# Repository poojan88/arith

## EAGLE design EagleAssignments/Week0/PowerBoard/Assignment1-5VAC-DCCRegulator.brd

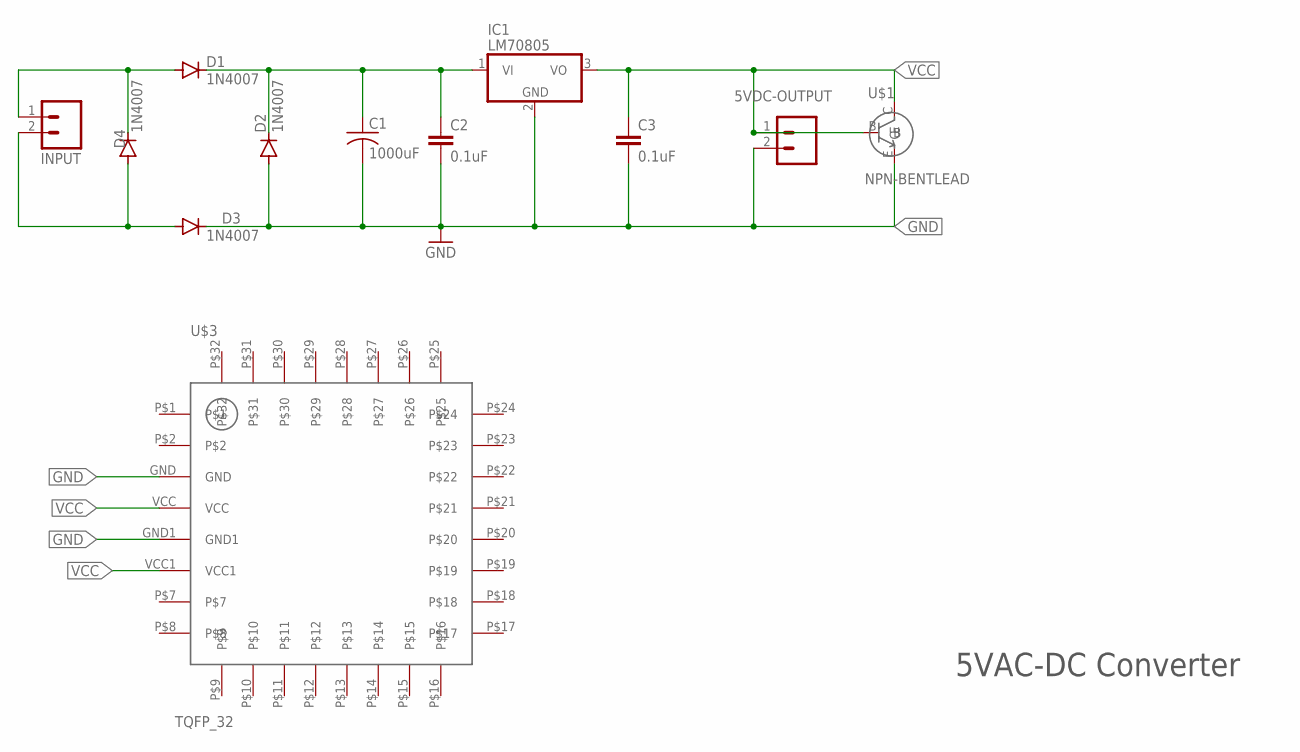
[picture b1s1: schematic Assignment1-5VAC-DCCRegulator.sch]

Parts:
5VDC-OUTPUT: M02; 02P
C1: 1000uF; C025-024X044
C2, C3: 0.1uF; C025-025X050
D1, D2, D3, D4: 1N4007; DO41-10
IC1: LM70805; TO220V
INPUT: M02; 02P
U$1: NPN-BENTLEAD; BENT-LEAD
U$3: TQFP_32

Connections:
GND: 5VDC-OUTPUT.2, C1.2, C2.2, C3.2, D2.A, D3.C, IC1.2 (GND), U$1.E, U$3.GND, U$3.GND1
unnamed: D1.A, D4.C, INPUT.1
unnamed: D3.A, D4.A, INPUT.2
unnamed: C1.1, C2.1, D1.C, D2.C, IC1.1 (VI)
VCC: 5VDC-OUTPUT.1, C3.1, IC1.3 (VO), U$1.B, U$1.C, U$3.VCC, U$3.VCC1

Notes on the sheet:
5VAC-DC Converter

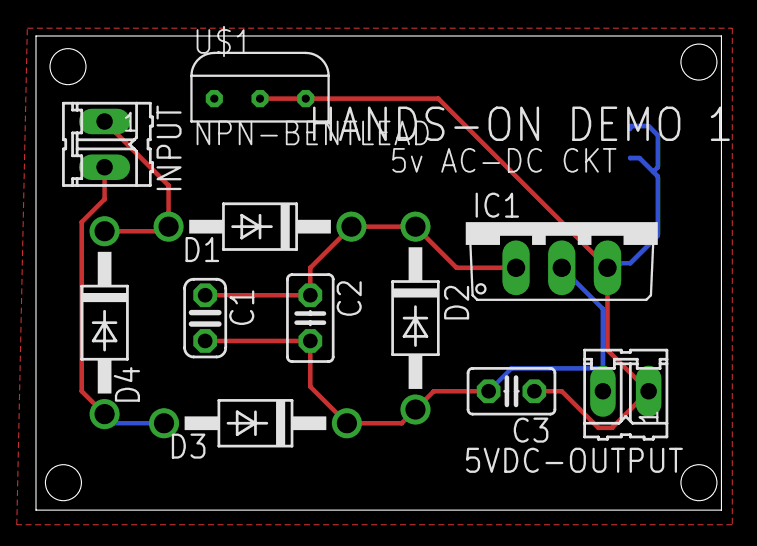
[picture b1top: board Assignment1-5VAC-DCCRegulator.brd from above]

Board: 2 copper layers, 38.1 x 26.3 mm, 12 parts (1 on the bottom side), 5 nets.

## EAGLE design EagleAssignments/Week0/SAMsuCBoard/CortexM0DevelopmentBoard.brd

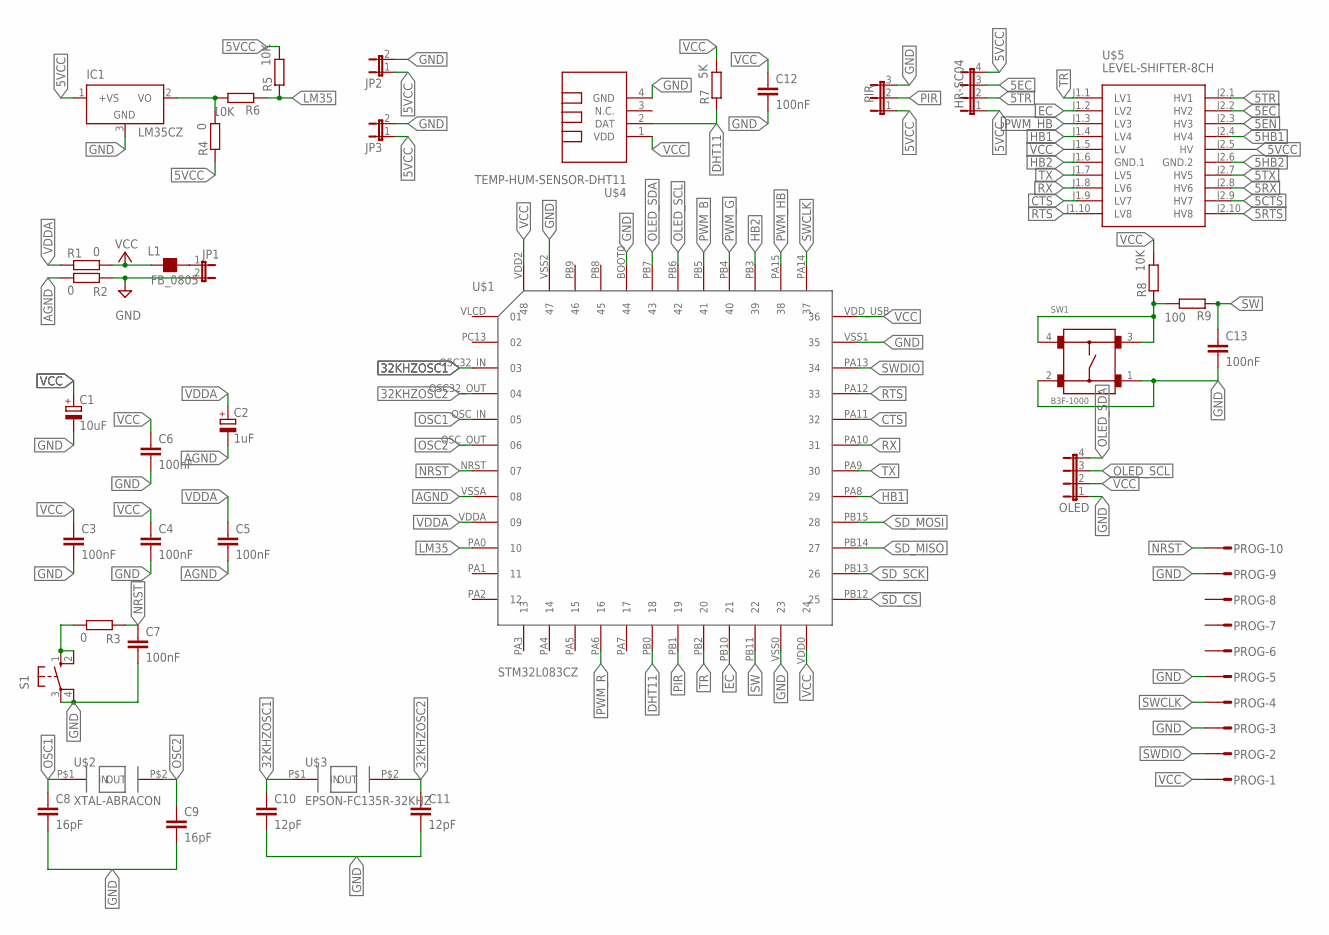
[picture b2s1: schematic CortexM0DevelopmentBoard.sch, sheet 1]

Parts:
C1: 10uF; 139CLL-2R
C2: 1uF; 139CLL-2R
C3, C4, C5, C6, C7, C12, C13: 100nF; C0805
C8, C9: 16pF; C0805
C10, C11: 12pF; C0805
HR-SC04: JP4E; JP4
IC1: LM35CZ; TO92
JP1, JP2, JP3: JP1E; JP1
L1: FB_0805; L0805
OLED: JP4E; JP4
PIR: JP2E; JP2
PROG: S10P
R1, R2, R3, R4: 0; R0805
R5, R6, R8: 10K; R0805
R7: 5K; R0805
R9: 100; R0805
S1: 10-XX; B3F-10XX
SW1: B3F-1000
U$1: STM32L083CZ; STM32L083CZ-LQFP48
U$2: XTAL-ABRACON; XTAL-ABRACON-SMD
U$3: EPSON-FC135R-32KHZ; EPSON-32KHZ-FC135R
U$4: TEMP-HUM-SENSOR-DHT11
U$5: LEVEL-SHIFTER-8CH

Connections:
5CTS: U$5.J2.9 (HV7); also elsewhere on the board
5EC: HR-SC04.3, U$5.J2.2 (HV2)
5EN: U$5.J2.3 (HV3); also elsewhere on the board
5HB1: U$5.J2.4 (HV4); also elsewhere on the board
5HB2: U$5.J2.6 (GND.2); also elsewhere on the board
5RTS: U$5.J2.10 (HV8); also elsewhere on the board
5RX: U$5.J2.8 (HV6); also elsewhere on the board
5TR: HR-SC04.2, U$5.J2.1 (HV1)
5TX: U$5.J2.7 (HV5); also elsewhere on the board
5VCC: HR-SC04.1, HR-SC04.4, IC1.1 (+VS), JP2.1, PIR.1, R5.2, U$5.J2.5 (HV); also elsewhere on the board
32KHZOSC1: C10.1, U$1.OSC32_IN (03), U$3.P$1 (IN)
32KHZOSC2: C11.1, U$1.OSC32_OUT (04), U$3.P$2 (OUT)
!5VCC: JP3.1, R4.1
!SD_CS: U$1.PB12 (25); also elsewhere on the board
AGND: C2.-, C5.2, R2.1, U$1.VSSA (08)
CTS: U$1.PA11 (32), U$5.J1.9 (LV7)
DHT11: R7.1, U$1.PB0 (18), U$4.2 (DAT)
EC: U$1.PB10 (21), U$5.J1.2 (LV2)
GND: C1.-, C3.2, C4.2, C6.2, C7.2, C8.2, C9.2, C10.2, C11.2, C12.2, C13.2, IC1.3 (GND), JP1.2, JP2.2, JP3.2, OLED.1, PIR.3, PROG.3, PROG.5, PROG.9, R2.2, S1.3, S1.4 (P1), SW1.1, SW1.2, U$1.BOOT0 (44), U$1.VSS0 (23), U$1.VSS1 (35), U$1.VSS2 (47), U$4.4 (GND); also elsewhere on the board
HB1: U$1.PA8 (29), U$5.J1.4 (LV4)
HB2: U$1.PB3 (39), U$5.J1.6 (GND.1)
LM35: R5.1, R6.1, U$1.PA0 (10)
unnamed: JP1.1, L1.2
unnamed: R3.1, S1.1 (S), S1.2 (S1)
unnamed: IC1.2 (VO), R4.2, R6.2
unnamed: R8.1, R9.2, SW1.3, SW1.4
NRST: C7.1, PROG.10, R3.2, U$1.NRST (07)
OLED_SCL: OLED.3, U$1.PB6 (42)
OLED_SDA: OLED.4, U$1.PB7 (43)
OSC1: C8.1, U$1.OSC_IN (05), U$2.P$1 (IN)
OSC2: C9.1, U$1.OSC_OUT (06), U$2.P$2 (OUT)
PIR: PIR.2, U$1.PB1 (19)
PWM_B: U$1.PB5 (41); also elsewhere on the board
PWM_G: U$1.PB4 (40); also elsewhere on the board
PWM_HB: U$1.PA15 (38), U$5.J1.3 (LV3)
PWM_R: U$1.PA6 (16); also elsewhere on the board
RTS: U$1.PA12 (33), U$5.J1.10 (LV8)
RX: U$1.PA10 (31), U$5.J1.8 (LV6)
SD_MISO: U$1.PB14 (27); also elsewhere on the board
SD_MOSI: U$1.PB15 (28); also elsewhere on the board
SD_SCK: U$1.PB13 (26); also elsewhere on the board
SW: C13.1, R9.1, U$1.PB11 (22)
SWCLK: PROG.4, U$1.PA14 (37)
SWDIO: PROG.2, U$1.PA13 (34)
TR: U$1.PB2 (20), U$5.J1.1 (LV1)
TX: U$1.PA9 (30), U$5.J1.7 (LV5)
VCC: C1.+, C3.1, C4.1, C6.1, C12.1, L1.1, OLED.2, PROG.1, R1.2, R7.2, R8.2, U$1.VDD0 (24), U$1.VDD2 (48), U$1.VDD_USB (36), U$4.1 (VDD), U$5.J1.5 (LV); also elsewhere on the board
VDDA: C2.+, C5.1, R1.1, U$1.VDDA (09)

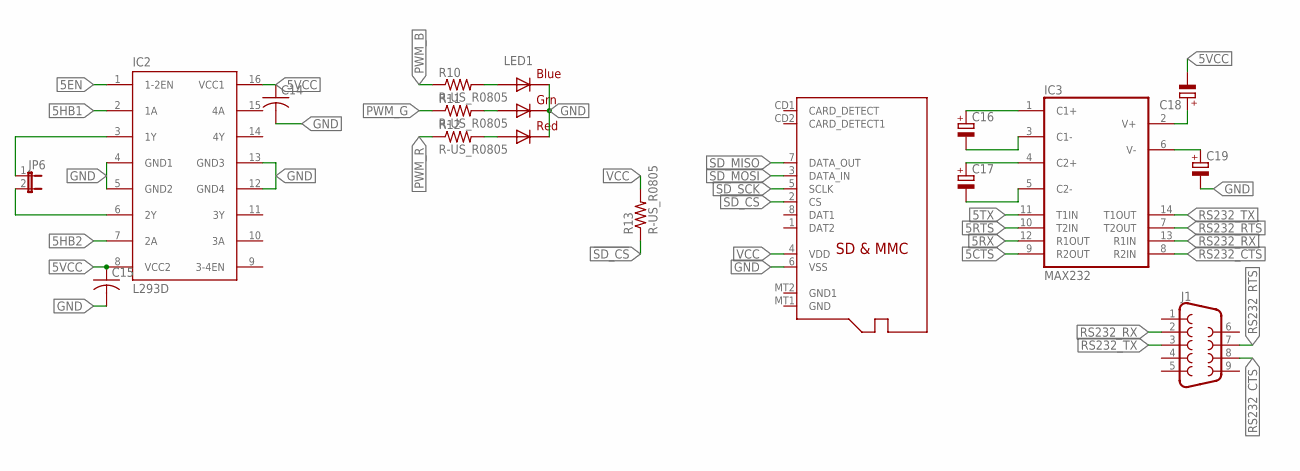
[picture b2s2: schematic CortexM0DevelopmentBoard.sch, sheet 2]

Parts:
C14, C15: C-US_CHIP-0805(2012-METRIC); CAPC2012X110
C16, C17, C18, C19: C-POL_TANTALUM-1206(3216-METRIC); CAPMP3216X180N
IC2: L293D; DIL16
IC3: MAX232; DIL16
J1: DB9FEMALE; DB9
JP6: JP1E; JP1
LED1: RGBLED5050
R10, R11, R12, R13: R-US_R0805; R0805
U$6: MICROSD

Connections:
5CTS: IC3.9 (R2OUT); also elsewhere on the board
5EN: IC2.1 (1-2EN); also elsewhere on the board
5HB1: IC2.2 (1A); also elsewhere on the board
5HB2: IC2.7 (2A); also elsewhere on the board
5RTS: IC3.10 (T2IN); also elsewhere on the board
5RX: IC3.12 (R1OUT); also elsewhere on the board
5TX: IC3.11 (T1IN); also elsewhere on the board
5VCC: C14.1, C15.1, C18.2 (-), IC2.8 (VCC2), IC2.16 (VCC1); also elsewhere on the board
!SD_CS: R13.1, U$6.2 (CS); also elsewhere on the board
GND: C14.2, C15.2, C19.2 (-), IC2.4 (GND1), IC2.5 (GND2), IC2.12 (GND4), IC2.13 (GND3), IC3.15 (GND), LED1.4 (BLUE_C), LED1.5 (RED_C), LED1.6 (GREEN_C), U$6.6 (VSS); also elsewhere on the board
unnamed: LED1.3 (BLUE_A), R10.2
unnamed: LED1.1 (GREEN_A), R11.2
unnamed: LED1.2 (RED_A), R12.2
unnamed: C16.1 (+), IC3.1 (C1+)
unnamed: C16.2 (-), IC3.3 (C1-)
unnamed: C17.1 (+), IC3.4 (C2+)
unnamed: C17.2 (-), IC3.5 (C2-)
unnamed: IC2.3 (1Y), JP6.1
unnamed: IC2.6 (2Y), JP6.2
unnamed: C18.1 (+), IC3.2 (V+)
unnamed: C19.1 (+), IC3.6 (V-)
PWM_B: R10.1; also elsewhere on the board
PWM_G: R11.1; also elsewhere on the board
PWM_R: R12.1; also elsewhere on the board
RS232_CTS: IC3.8 (R2IN), J1.8
RS232_RTS: IC3.7 (T2OUT), J1.7
RS232_RX: IC3.13 (R1IN), J1.2
RS232_TX: IC3.14 (T1OUT), J1.3
SD_MISO: U$6.7 (DATA_OUT); also elsewhere on the board
SD_MOSI: U$6.3 (DATA_IN); also elsewhere on the board
SD_SCK: U$6.5 (SCLK); also elsewhere on the board
VCC: IC3.16 (VCC), R13.2, U$6.4 (VDD); also elsewhere on the board

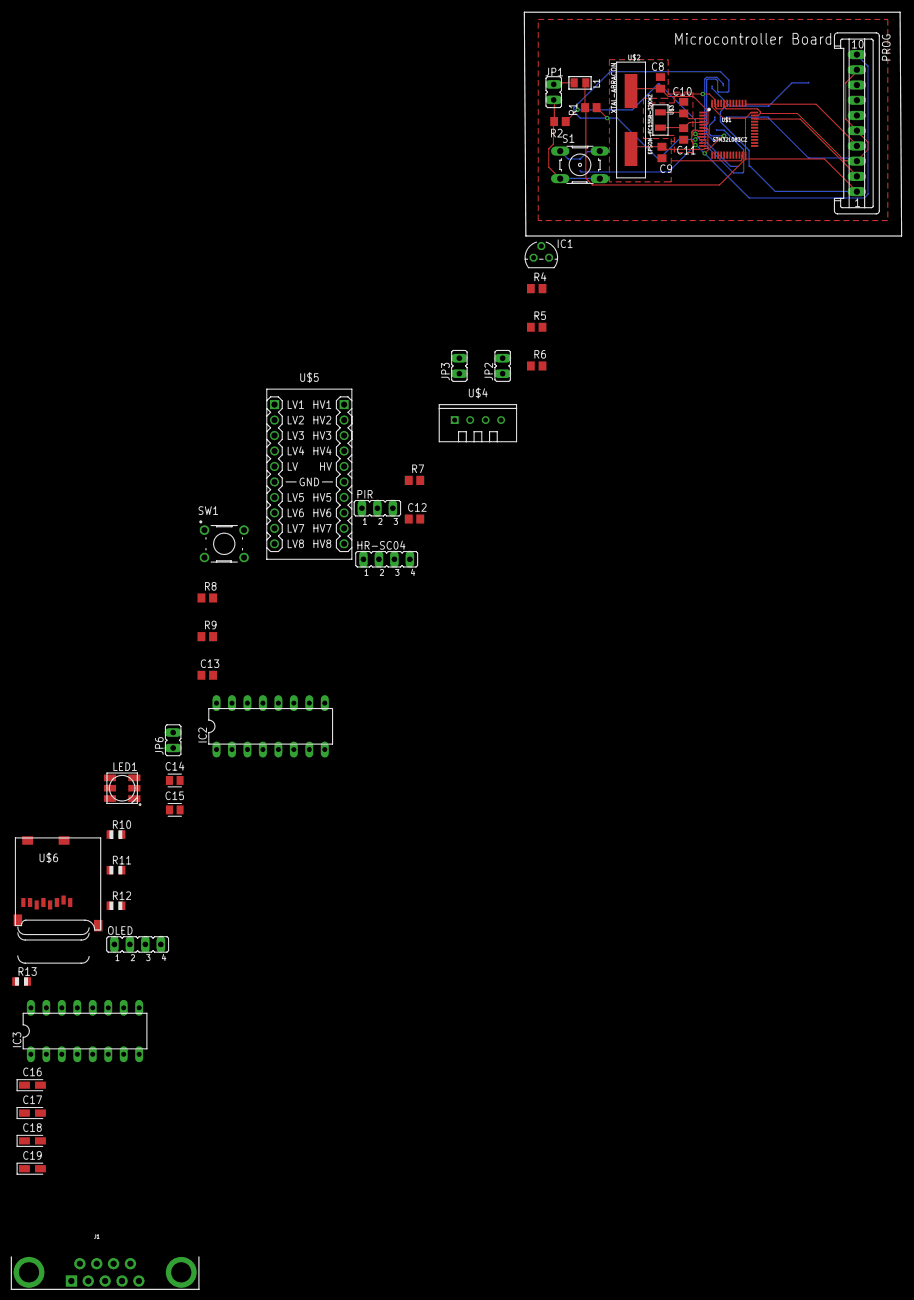
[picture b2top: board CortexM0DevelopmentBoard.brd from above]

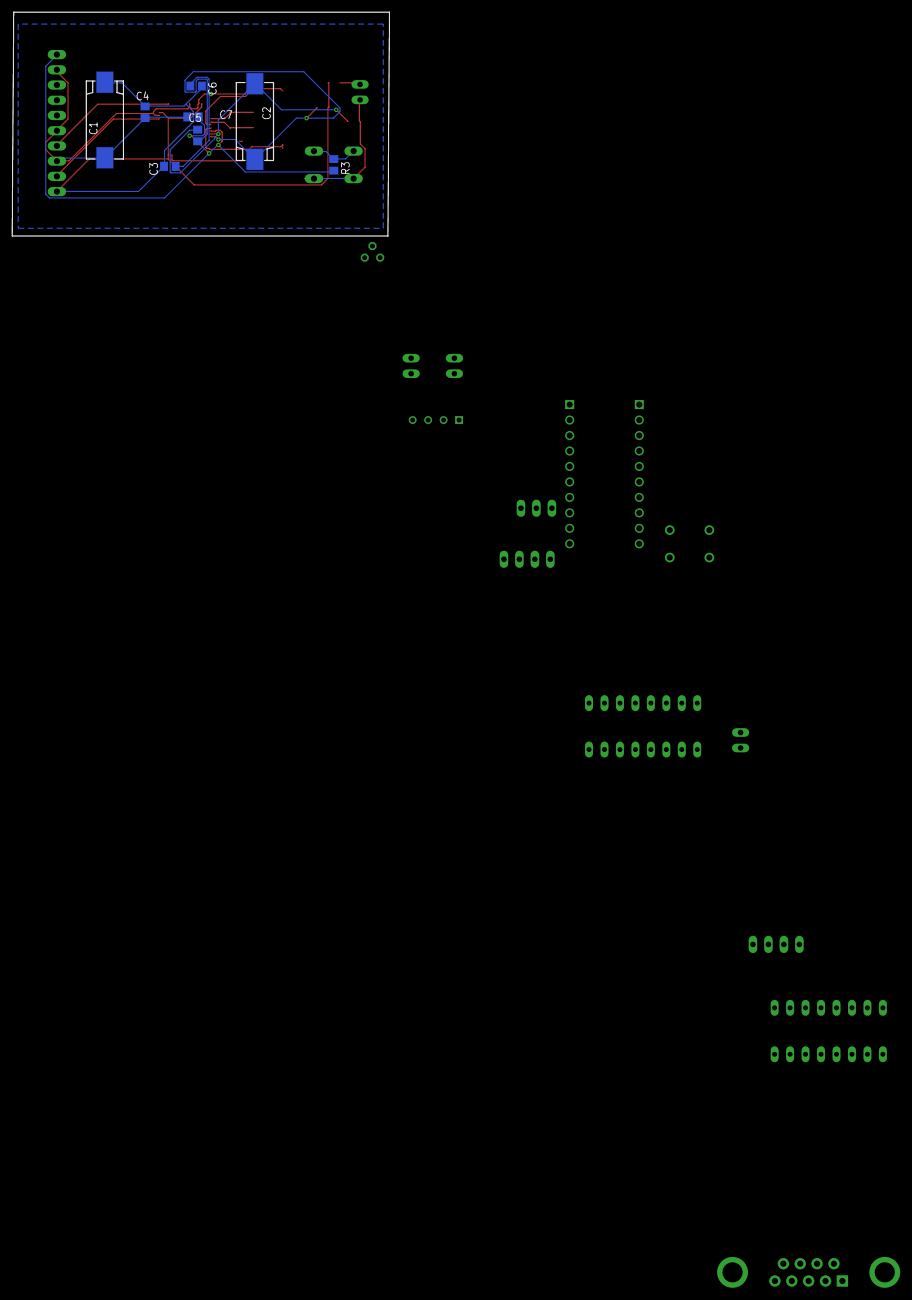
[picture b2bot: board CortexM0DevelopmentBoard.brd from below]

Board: 2 copper layers, 62.0 x 36.8 mm, 54 parts (8 on the bottom side), 63 nets.

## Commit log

2021-02-20 Added gitignore file
2021-02-20 Added README.MD for documentation
2021-02-20 SAM added some files..

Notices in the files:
parts and their libraries:
rc-master: Copyright (C) 2007, Bob Starr
DHT11: Released under the Creative Commons Attribution 4.0 International License: http://creativecommons.org/licenses/by/4.0
SparkFun-Connectors: Licensing: Creative Commons ShareAlike 4.0 International - https://creativecommons.org/licenses/by-sa/4.0
